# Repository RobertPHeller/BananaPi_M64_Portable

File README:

Banana Pi M64 based portable.

Includes:

Case design

5VDC to 12VDC power supply
Teensy 3.2 based thumbstick pointer w/ three buttons

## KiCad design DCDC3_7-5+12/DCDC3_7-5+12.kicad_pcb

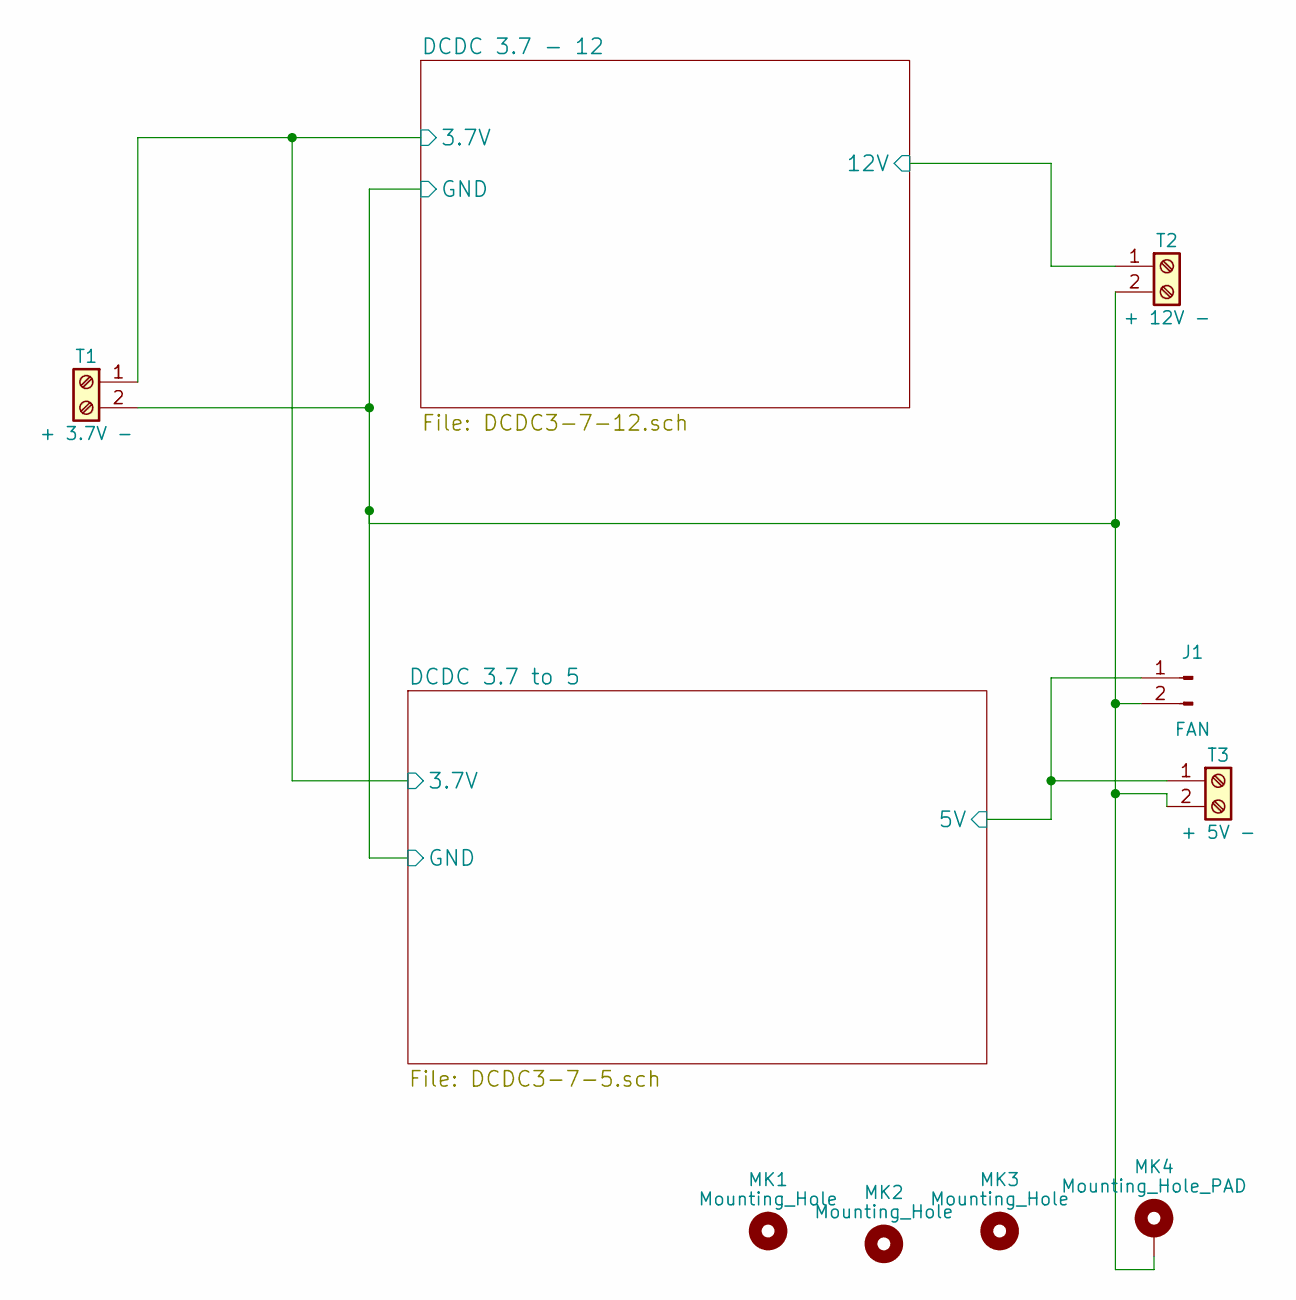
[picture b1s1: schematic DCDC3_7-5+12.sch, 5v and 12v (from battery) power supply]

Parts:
J1: FAN; Pin_Header_Straight_1x02_Pitch2.54mm
MK1, MK2, MK3: Mounting_Hole; MountingHole_3.5mm
MK4: Mounting_Hole_PAD; MountingHole_3.5mm_Pad
T1: + 3.7V -; TerminalBlock_Pheonix_MPT-2.54mm_2pol
T2: + 12V -; TerminalBlock_Pheonix_MPT-2.54mm_2pol
T3: + 5V -; TerminalBlock_Pheonix_MPT-2.54mm_2pol

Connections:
/DCDC 3.7 - 12/3.7V: T1.1; also elsewhere on the board
/DCDC 3.7 - 12/12V: T2.1; also elsewhere on the board
/DCDC 3.7 to 5/5V: J1.1, T3.1; also elsewhere on the board
GND: J1.2, MK4.1, T1.2, T2.2, T3.2; also elsewhere on the board

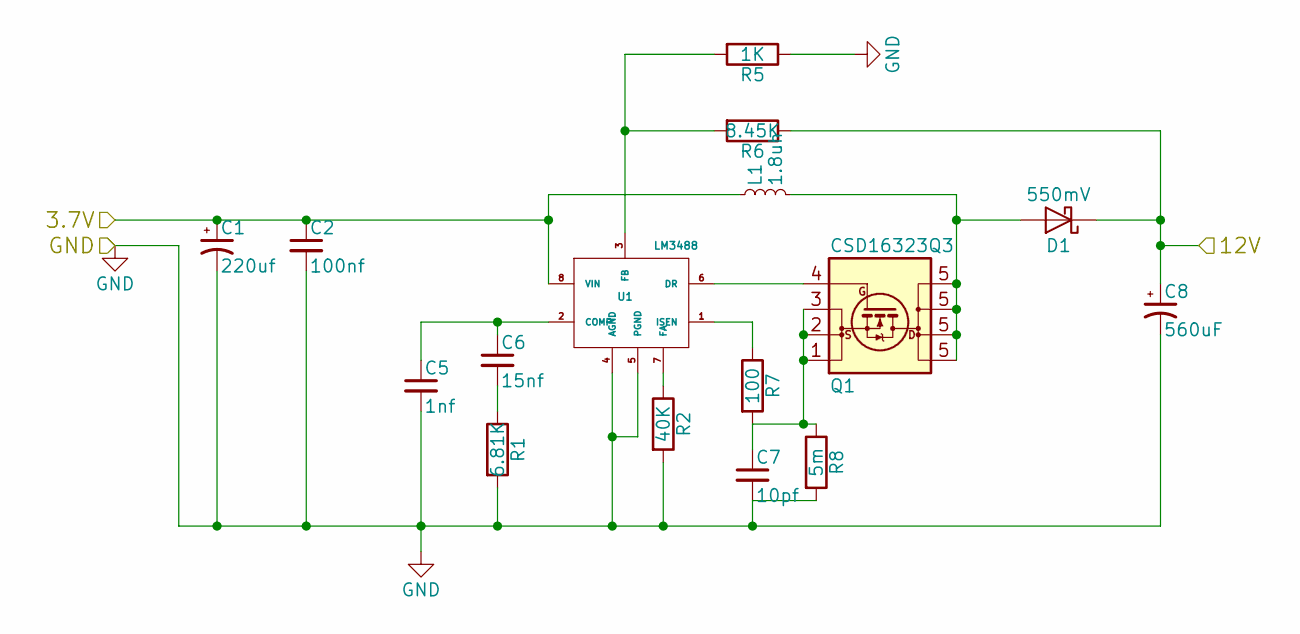
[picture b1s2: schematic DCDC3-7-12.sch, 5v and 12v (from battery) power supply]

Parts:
C1: 220uf; CP_Elec_5x5.7; Mouser Part Number 667-6SVPE220MW
C2: 100nf; C_0402; Mouser Part Number 81-GRM155R70J104KA1D
C5: 1nf; C_0402; Mouser Part Number 81-GRM1555C1H102JA1J
C6: 15nf; C_0805; Mouser Part Number 810-CGA4F2C0G1H153J
C7: 10pf; C_0805; Mouser Part Number 187-CL21C100CBANNNC
C8: 560uF; CP_Elec_10x10.5; Mouser Part Number 667-20SVPF560M
D1: 550mV; D_SMC; Mouser Part Number 241-SK54_R1_00001
L1: 1.8uh; INDM5564X32N; Mouser Part Number 994-XAL6030-182MEC
Q1: CSD16323Q3; Q3; Mouser Part Number 595-CSD16323Q3
R1: 6.81K; R_0402; Mouser Part Number 71-CRCW0402-6.81K-E3
R2: 40K; R_0805; Mouser Part Number 71-CRCW080540K0FKEA
R5: 1K; R_0402; Mouser Part Number 71-CRCW0402-1.0K
R6: 8.45K; R_0402; Mouser Part Number 71-CRCW0402-8.45K-E3
R7: 100; R_0402; Mouser Part Number 71-CRCW0402100RFKEDC
R8: 5m; R_0612; Mouser Part Number 71-WFCP06125L000FE66
U1: LM3488; TSSOP-8_3x3mm_Pitch0.65mm; Mouser Part Number 926-LM3488MM

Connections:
/DCDC 3.7 - 12/3.7V: C1.1, C2.1, L1.1, U1.8 (VIN); also elsewhere on the board
/DCDC 3.7 - 12/12V: C8.1, D1.1 (K), R6.1; also elsewhere on the board
GND: C1.2, C2.2, C5.2, C7.2, C8.2, R1.2, R2.2, R5.1, R8.2, U1.4 (AGND), U1.5 (PGND); also elsewhere on the board
unnamed: C5.1, C6.1, U1.2 (COMP)
unnamed: C6.2, R1.1
unnamed: C7.1, Q1.1 (S), Q1.2 (S), Q1.3 (S), R7.2, R8.1
unnamed: D1.2 (A), L1.2, Q1.5 (D)
unnamed: Q1.4 (G), U1.6 (DR)
unnamed: R2.1, U1.7 (FA)
unnamed: R5.2, R6.2, U1.3 (FB)
unnamed: R7.1, U1.1 (ISEN)

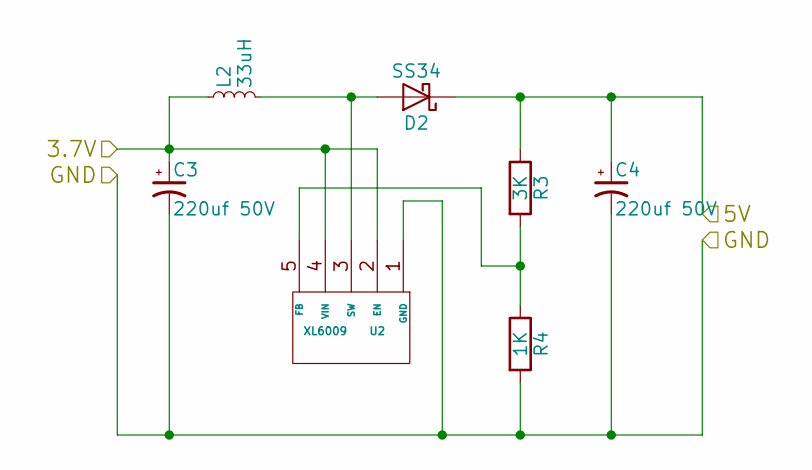
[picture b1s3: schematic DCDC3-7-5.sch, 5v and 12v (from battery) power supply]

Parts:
C3, C4: 220uf 50V; CP_Elec_10x10.5; Mouser Part Number 667-EEE-FK1H221V
D2: SS34; D_SMB_Handsoldering; Mouser Part Number 750-SS34BF-HF
L2: 33uH; INDPM183140X690N; Mouser Part Number 542-PM5022S-330M-RC
R3: 3K; R_0805_HandSoldering; Mouser Part Number 71-CRCW0805-3K
R4: 1K; R_0805_HandSoldering; Mouser Part Number 71-CRCW08051K00FKEAH
U2: XL6009; TO-263-5_TabPin3

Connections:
/DCDC 3.7 - 12/3.7V: C3.1, L2.1, U2.2 (EN), U2.4 (VIN); also elsewhere on the board
/DCDC 3.7 to 5/5V: C4.1, D2.1 (K), R3.1; also elsewhere on the board
GND: C3.2, C4.2, R4.2, U2.1 (GND); also elsewhere on the board
unnamed: D2.2 (A), L2.2, U2.3 (SW)
unnamed: R3.2, R4.1, U2.5 (FB)

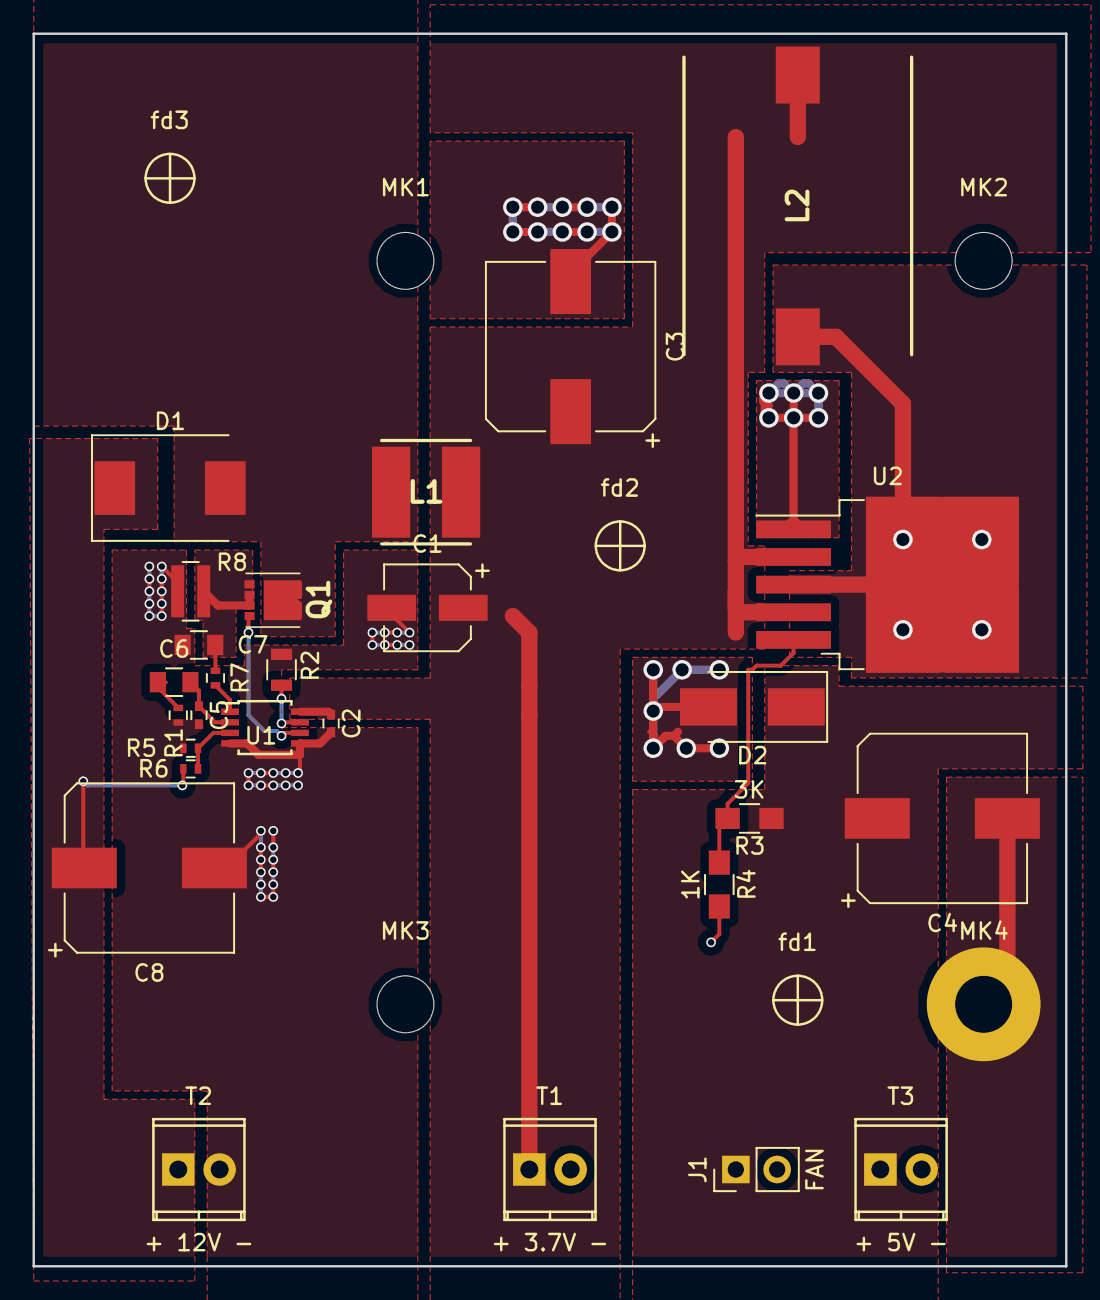
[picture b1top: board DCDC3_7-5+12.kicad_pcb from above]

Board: 2 copper layers, 63.5 x 75.8 mm, 34 parts (0 on the bottom side), 14 nets.

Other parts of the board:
fd1, fd2, fd3: Fiducial_classic_Small_SilkscreenTop_Type1

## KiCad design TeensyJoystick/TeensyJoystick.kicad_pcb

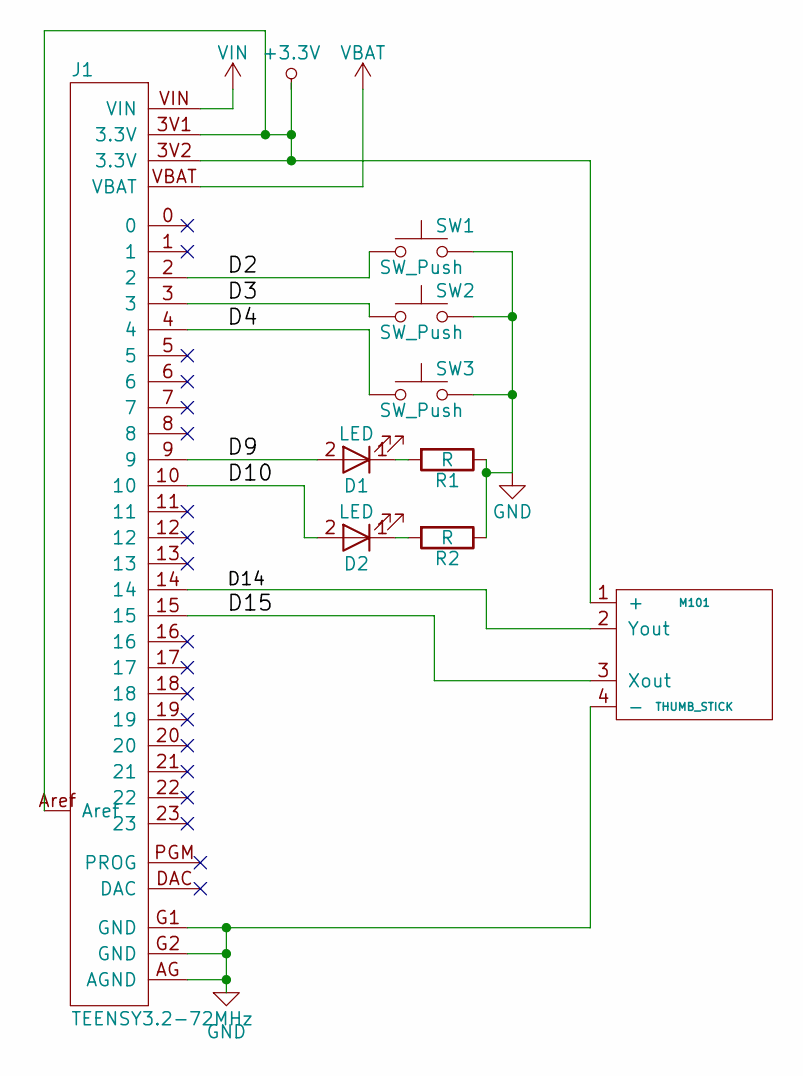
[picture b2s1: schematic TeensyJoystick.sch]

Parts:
D1, D2: LED; LED_D3.0mm
J1: TEENSY3.2-72MHz; TEENSY-3.2-NOSILK
M101: THUMB_STICK; MiniThumbStickBreakout
R1, R2: R; R_Axial_DIN0204_L3.6mm_D1.6mm_P7.62mm_Horizontal
SW1, SW2, SW3: SW_Push; SW_PUSH_6mm

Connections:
/D2: J1.2, SW1.1
/D3: J1.3, SW2.1
/D4: J1.4, SW3.1
/D9: D1.2 (A), J1.9
/D10: D2.2 (A), J1.10
/D14: J1.14, M101.2 (Yout)
/D15: J1.15, M101.3 (Xout)
GND: J1.AG (AGND), J1.G1 (GND), J1.G2 (GND), M101.4 (-), R1.1, R2.1, SW1.2, SW2.2, SW3.2
unnamed: D1.1 (K), R1.2
unnamed: D2.1 (K), R2.2
unnamed: J1.3V1 (3.3V), J1.3V2 (3.3V), J1.Aref, M101.1 (+)
VBAT: J1.VBAT
VIN: J1.VIN

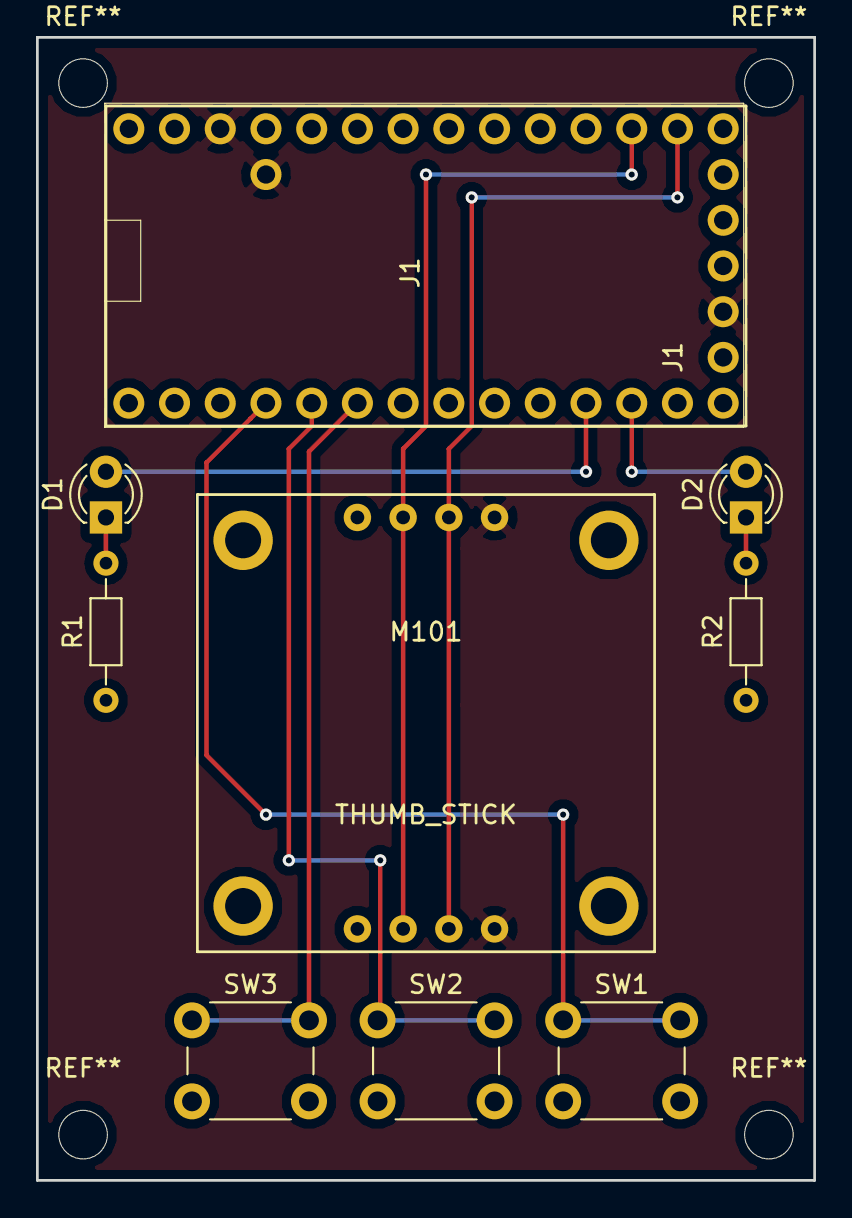
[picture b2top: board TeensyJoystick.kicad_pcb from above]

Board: 2 copper layers, 43.2 x 63.5 mm, 9 parts (0 on the bottom side), 11 nets.

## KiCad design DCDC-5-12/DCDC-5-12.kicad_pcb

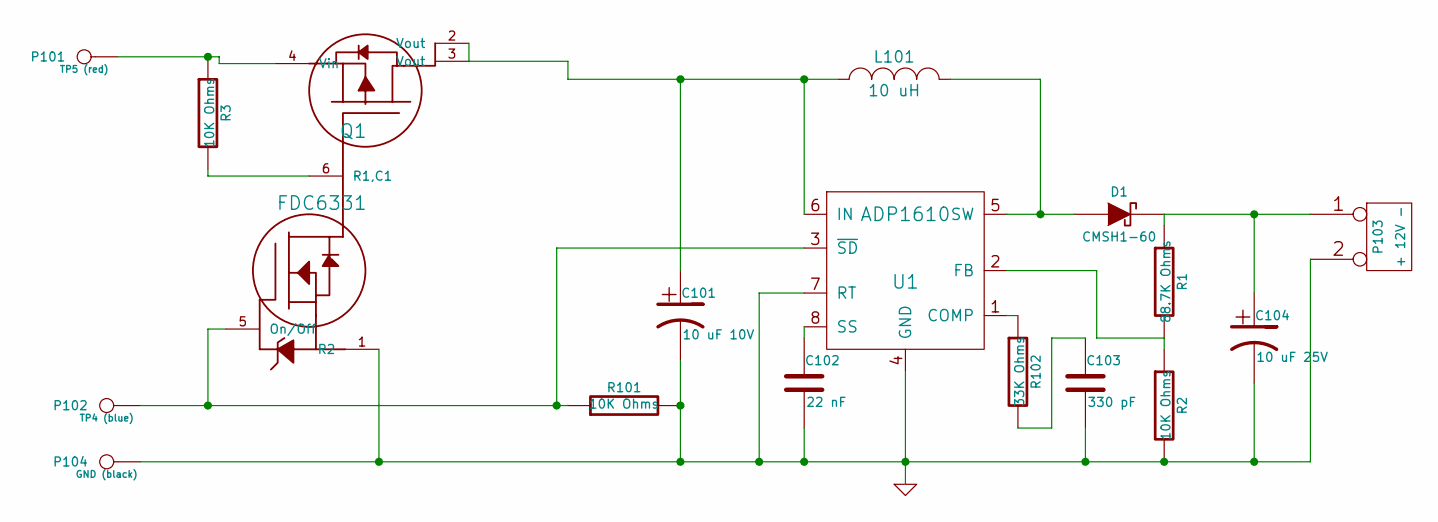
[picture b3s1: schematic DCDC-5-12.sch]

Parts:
C101: 10 uF 10V; Mouser Part Number 710-865090240001
C102: 22 nF; Mouser Part Number 80-C0603C223K5R
C103: 330 pF; Mouser Part Number 710-885012006082
C104: 10 uF 25V; Mouser Part Number 710-865080440002
D1: CMSH1-60; Mouser Part Number 610-CMSH1-60TR13
L101: 10 uH; Mouser Part Number 851-CDRH4D28NP-100NC
P101: TP5 (red)
P102: TP4 (blue)
P103: + 12V -
P104: GND (black)
Q1: FDC6331; Mouser Part Number 512-FDC6331L
R1: 88.7K Ohms; Mouser Part Number 652-CR0603FX-8872ELF
R2: 10K Ohms; Mouser Part Number 652-CR0603AFX1002EAS
R3, R101: 10K Ohms; Mouser Part Number 71-CRCW060310K0JNEBC
R102: 33K Ohms; Mouser Part Number 71-CRCW060333K0JNEB
U1: ADP1610; Mouser Part Number 584-ADP1610ARMZ-R7

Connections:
GND: C101.2, C102.2, C103.2, C104.2, P103.2 (PM), P104.1, Q1.1 (R2), R2.2, R101.2, U1.4 (GND), U1.7 (RT)
unnamed: C103.1, R102.2
unnamed: R102.1, U1.1 (COMP)
unnamed: R1.2, R2.1, U1.2 (FB)
unnamed: C102.1, U1.8 (SS)
unnamed: D1.1 (A), L101.2, U1.5 (SW)
unnamed: C101.1, L101.1, Q1.2 (Vout), Q1.3 (Vout), U1.6 (IN)
unnamed: Q1.6 (R1,C1), R3.2
unnamed: C104.1, D1.2 (K), P103.1, R1.1
unnamed: P101.1, Q1.4 (Vin), R3.1
unnamed: P102.1, Q1.5 (On/Off), R101.1, U1.3 (~SD)

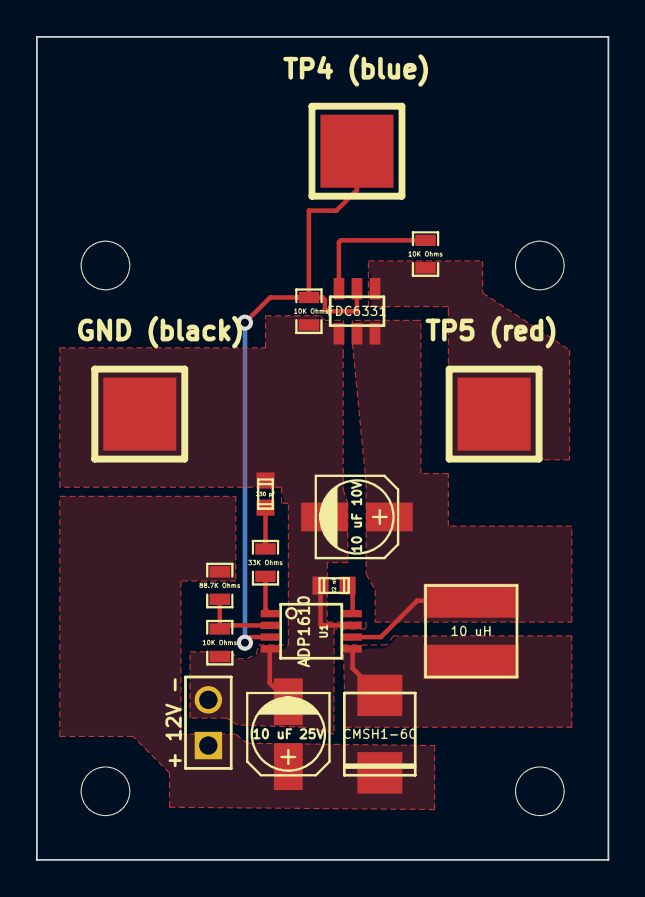
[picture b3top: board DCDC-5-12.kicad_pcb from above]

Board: 2 copper layers, 31.8 x 45.7 mm, 21 parts (0 on the bottom side), 11 nets.

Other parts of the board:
MH: MountingHole_2-7mm_RevA_Date21Jun2010
MH#2, MH#3, MH#4: MountingHole_2-7mm_RevA_Date21Jun2010

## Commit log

2020-05-04 Add .gitignore
2020-05-05 Work on PS box
2020-05-05 Working on PS Box
2020-05-07 Continuing work on the mechanicals.
2020-05-08 Complete the PS box.
2020-05-08 Further work on PS Box
2020-05-08 Integrate PS Box with main case.
2020-05-09 Fan grill holes
2020-05-09 Refactoring 3D model code started.
2020-05-09 Refactoring 3D model code continuing.
2020-05-11 Complete 3D model code (for now).
2020-05-15 Add DCDC converter, start on dimensions.
2020-05-15 Add LCD Screen mounting brackets, along with the screen itself.
2020-05-15 Install LCD Mounting Brackets and LCD Screen in case.
2020-05-15 LCD Bracket mounting holes.
2020-05-15 Add HDMI Converter boards.
2020-05-16 Mount HDMI Converter Boards in Case.
2020-05-16 Insert DIMs.
2020-05-18 Add thumbstick board.
2020-05-19 Add Speakers
2020-05-21 Battery and corner blocks.
2020-05-21 More corner blocks.
2020-05-21 Finish corner blocks.
2020-05-21 LCD Mounting bracket improvements: notch aroung speaker standoffs, SVG drawing output. Updates to SVGOutput: polygons.
2020-05-21 LCD Bracket SVG output completed.
2020-05-22 Complete Bracket drawings, with dimensions.
2020-05-23 Block drill sheets.
2020-05-24 Add (internal) USBHub.
2020-05-26 Harddrive, USB=>SATA, OTG adapter added.
2020-05-26 USB=>SATA board position adjusted.
2020-05-27 USB SATA Cradle.
2020-05-27 Additional mounting holes.
2020-05-27 Generate gcad for 3D printed parts.
2020-05-28 Adjust Keyboardshelf to accomdate the keyboard. Reposition USBHub to avoid Keyboardshelf.
2020-05-30 Add in hinges
2020-05-30 Begin to translate from Tcl/gCAD3d to Python/FreeCAD.
2020-05-31 Added PCB (with strips and mounting holes).
2020-05-31 Starting to populate the Power PCB: PS, terms, caps. done.
2020-06-01 PS PCB Completed.
2020-06-02 Building up the PS Box.
2020-06-02 Completed PS Box.
2020-06-02 Moving onto the full case.
2020-06-03 Add DCDC 5-12 converter.
2020-06-03 Add LCD Mounting Brackets.
2020-06-03 HDMI and Cut List.
2020-06-05 Almost Done: need to do the TeensyThumbStick, PianoHinge, and complete the KeyboardShelf. Then I need to generate the drawings, etc.
2020-06-05 Very nearly done.
2020-06-05 Basic design model basicallt complete.
2020-06-05 Added mounting holes for the hinges.
2020-06-06 Refactor Part.show() with explicit doc.addObject()... calls.
2020-06-07 SVG Templates for drawings.
2020-06-07 Panel cut sheet done.
2020-06-07 Started Machine Shop work drawings.
2020-06-08 Fix inlet body cutout error. Complete PS Box basedrawing.
2020-06-08 Complete PS Box cover drawing.
2020-06-08 Completed Machine Work Drawings.
2020-06-08 Block Drill Sheet Drawings done.
2020-06-09 Plastic machine work drawings
2020-06-09 Add 3D printing file (stl) creation script.
2020-06-09 Starting on adding Dimensions...
2020-06-10 Start on cover image.
2020-06-10 Start working on using TechDraw to create 2D drawings...
2020-06-11 First draft of TechDraw drawings of the LCD Mounting Bracket.
2020-06-11 Fine Tuning LDC Mounting Bracket Drawing.
2020-06-13 Starting on Mech. Drawings for the Power Supply Box: Base done, stalled on the Cover...
2020-06-14 Completed Power Supply Cover Drawing
2020-06-15 Complete Power Supply Machining Drawings
2020-06-15 Complete Teensy ThumbStick Cover Machining Drawing
2020-06-20 Cover Artwork
2020-06-20 Completed all Revision A case design work.
2020-06-22 Code to create 3D print files (STL)
2020-06-28 A quick simple adapter for the console tty
2020-07-07 Add grommets for fan power wires
2020-07-26 Second PS, Bigger PS box, PS Drawing
2020-08-20 CAD Updates. Close to being done.
2020-12-15 Split Panel sheet into 3 24x16
2020-12-15 Add removeCPs.sh
2020-12-15 Remove battery panel holes from bottom panel.
2021-04-18 Assorted drawing issues (missing/wrong dims).
2021-07-30 TeensyJoystick updates
2021-07-30 Add Missing file
2021-07-30 Working on 3D model of TeensyJoystick Box.
2021-07-30 Finish Teensy Joystick.
2021-07-31 Working on the TeensyJoystick Box.
2021-07-31 TeensyJoystick box completed.
2022-01-20 Update Teensy Joystick
2022-01-25 mouse speed updates
2022-06-15 12V and 5V buck power supplies
2022-06-16 Add mounting holes, adjust things to accomadate mounting holes.
2022-06-16 add alternitive inductor footprint
2022-06-16 Add FAN header, minor trace updates.
2022-07-12 Nearly complete circuit for the AUX power supply.
2022-07-14 Final version of aux 5v and 12v power supply.

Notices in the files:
TeensyJoystick/TeensyJoystick.kicad_pcb:
Released under the CERN Open Hardware License v1.2
